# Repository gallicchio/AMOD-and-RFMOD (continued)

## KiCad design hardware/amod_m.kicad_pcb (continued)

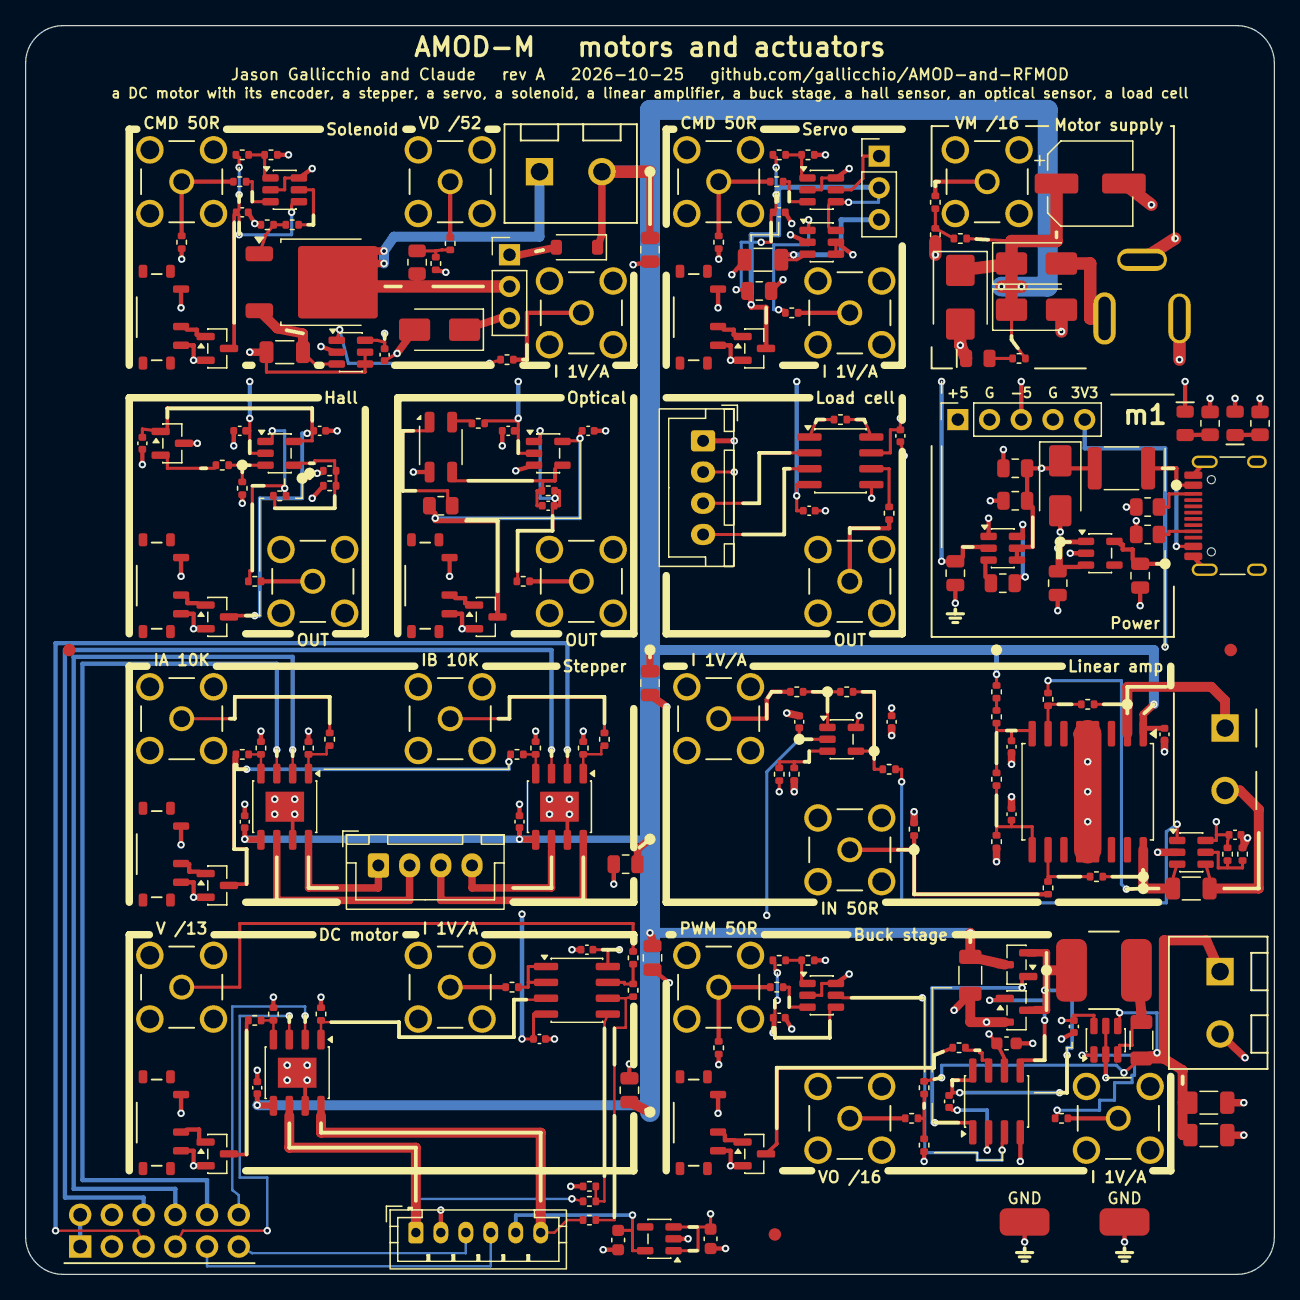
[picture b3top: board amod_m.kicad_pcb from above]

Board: 4 copper layers, 100.0 x 100.0 mm, 207 parts (0 on the bottom side), 126 nets.

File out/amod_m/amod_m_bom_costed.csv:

Comment,Designator,Footprint,LCSC Part #,MPN,Qty,Unit $,Ext $,JLC
220u,C201,CP_Elec_6.3x7.7,C2992606,XT220UF25V90RV0075,1,0.0534,0.053,extended
220n,C804,C_0402_1005Metric,C16772,CL05B224KO5NNNC,1,0.0047,0.005,basic
100p,C1001,C_0402_1005Metric,C1546,0402CG101J500NT,1,0.0033,0.003,basic
1u,"C105,C106",C_0805_2012Metric,C28323,CL21B105KBFNNNE,2,0.0341,0.068,basic
1u,"C305,C306,C805",C_0603_1608Metric,C15849,CL10A105KB8NNNC,3,0.0146,0.044,basic
22u,"C803,C806,C807",C_1206_3216Metric,C12891,CL31A226KAHNNNE,3,0.1673,0.502,basic
10u,"C101,C102,C103,C104,C302,C403,C502,C603,C701,C801",C_0805_2012Metric,C15850,CL21A106KAYNNNE,10,0.0426,0.426,basic
100n,"C301,C303,C304,C401,C402,C501,C601,C602,C702,C703,C704,C705,C706,C707,C802,C808,C901,C902,C903,C1002,C1003,C1101,C1102",C_0402_1005Metric,C1525,CL05B104KO5NNNC,23,0.0035,0.081,basic
SMAJ5.0A,D101,D_SMA,C78401,SMAJ5.0A,1,0.0537,0.054,extended
SMBJ16A,D201,D_SMB,C353386,SMBJ16A,1,0.0395,0.040,extended
B5819W,D601,D_SOD-123,C64885,B5819W,1,0.0195,0.019,extended
SMAJ24A,D602,D_SMA,C113962,SMAJ24A,1,0.0407,0.041,extended
SS34,"D202,D203",D_SMA,C8678,SS34,2,0.0351,0.070,basic
2A,F101,Fuse_1812_4532Metric,C210837,MF-MSMF200-2,1,0.0650,0.065,extended
USB-C,J101,USB_C_Receptacle_HRO_TYPE-C-31-M-12,C165948,TYPE-C-31-M-12,1,0.1888,0.189,extended
rails,J102,PinSocket_1x05_P2.54mm_Vertical,C2894928,PZ254-1-05-Z-8.5,1,0.0588,0.059,extended
5-16V,J202,BarrelJack_DC-005-5A_Horizontal,C381116,DC-005-5A-2.0,1,0.2631,0.263,extended
motor,J303,JST_PH_B6B-PH-K_1x06_P2.00mm_Vertical,C131342,B6B-PH-K-S(LF)(SN),1,0.0728,0.073,extended
Pmod,J304,PinHeader_2x06_P2.54mm_Horizontal_PZ254R-12-12P,C492434,PZ254R-12-12P,1,0.1036,0.104,extended
stepper,J403,JST_XH_B4B-XH-A_1x04_P2.50mm_Vertical,C144395,B4B-XH-A(LF)(SN),1,0.0569,0.057,extended
servo,J503,PinHeader_1x03_P2.54mm_Vertical,C2937625,PZ254V-11-03P,1,0.0199,0.020,extended
coil,J604,TerminalBlock_KF301_1x02_P5.00mm,C474881,KF301-5.0-2P,1,0.1017,0.102,extended
D Z,J605,PinHeader_1x03_P2.54mm_Vertical,C2937625,PZ254V-11-03P,1,0.0199,0.020,extended
load,J703,TerminalBlock_KF301_1x02_P5.00mm,C474881,KF301-5.0-2P,1,0.1017,0.102,extended
out,J804,TerminalBlock_KF301_1x02_P5.00mm,C474881,KF301-5.0-2P,1,0.1017,0.102,extended
cell,J1102,JST_XH_B4B-XH-A_1x04_P2.50mm_Vertical,C144395,B4B-XH-A(LF)(SN),1,0.0569,0.057,extended
SMA,"J201,J301,J302,J401,J402,J501,J502,J601,J602,J603,J701,J702,J801,J802,J803,J901,J1001,J1101",SMA_BWSMA-KE-Z001_Vertical,C496549,BWSMA-KE-Z001,18,0.4043,7.277,extended
47u,L801,L_6x6_SWPA6045,C36414,SWPA6045S470MT,1,0.0801,0.080,extended
-5V,LED101,LED_0805_2012Metric_Kbar,C84256,NCD0805R1,1,0.0135,0.013,basic
+5V,LED102,LED_0805_2012Metric_Kbar,C2297,KT-0805G,1,0.0164,0.016,basic
VM,LED201,LED_0805_2012Metric_Kbar,C2297,KT-0805G,1,0.0164,0.016,basic
NCE6020AK,Q602,TO-252-2,C108639,NCE6020AK,1,0.1560,0.156,extended
AO3400A,"Q802,Q803",SOT-23,C20917,AO3400A,2,0.0889,0.178,basic
AO3401A,"Q301,Q401,Q501,Q601,Q801,Q901,Q1001",SOT-23,C15127,AO3401A,7,0.0959,0.671,basic
4.7k,R204,R_0402_1005Metric,C25900,0402WGF4701TCE,1,0.0021,0.002,basic
1.5k,R302,R_0402_1005Metric,C25867,0402WGF1501TCE,1,0.0029,0.003,basic
0.1,R710,R_1206_3216Metric,C25334,1206W4F100LT5E,1,0.0080,0.008,basic
2k,R716,R_0402_1005Metric,C4109,0402WGF2001TCE,1,0.0026,0.003,basic
180,R1002,R_0805_2012Metric,C25270,0805W8F1800T5E,1,0.0031,0.003,extended
249,R1101,R_0402_1005Metric,C25096,0402WGF2490TCE,1,0.0015,0.002,extended
1k,"R103,R104",R_0805_2012Metric,C17513,0805W8F1001T5E,2,0.0035,0.007,basic
13k,"R308,R309",R_0402_1005Metric,C25754,0402WGF1302TCE,2,0.0023,0.005,extended
100k,"R606,R805",R_0402_1005Metric,C25741,0402WGF1003TCE,2,0.0015,0.003,basic
100,"R610,R1001",R_0402_1005Metric,C25076,0402WGF1000TCE,2,0.0012,0.002,basic
5.1k,"R101,R102,R609",R_0805_2012Metric,C27834,0805W8F5101T5E,3,0.0036,0.011,basic
620,"R303,R403,R406",R_0402_1005Metric,C4961,0402WGF6200TCE,3,0.0019,0.006,extended
47k,"R503,R603,R803",R_0402_1005Metric,C25792,0402WGF4702TCE,3,0.0020,0.006,basic
5.1k,"R504,R604,R804",R_0402_1005Metric,C25905,0402WGF5101TCE,3,0.0023,0.007,basic
0.05,"R505,R607,R806",R_1206_3216Metric,C127691,1206W3F500MT5E,3,0.0110,0.033,extended
15k,"R203,R701,R702,R808",R_0402_1005Metric,C25756,0402WGF1502TCE,4,0.0010,0.004,basic
3.9k,"R402,R405,R902,R905",R_0402_1005Metric,C51721,0402WGF3901TCE,4,0.0012,0.005,extended
20k,"R703,R707,R713,R903,R904",R_0402_1005Metric,C25765,0402WGF2002TCE,5,0.0011,0.006,basic
1k,"R202,R301,R305,R307,R401,R404,R711,R712,R809,R1003",R_0402_1005Metric,C11702,0402WGF1001TCE,10,0.0013,0.013,basic
10k,"R407,R408,R502,R602,R704,R706,R708,R709,R714,R715,R802,R901",R_0402_1005Metric,C25744,0402WGF1002TCE,12,0.0011,0.013,basic
49.9,"R201,R304,R306,R501,R506,R601,R605,R608,R611,R705,R717,R801,R807,R810,R906,R1004,R1102",R_0402_1005Metric,C844112,CRCW040249R9FKEDHP,17,0.0318,0.541,extended
ON,"SW301,SW401,SW501,SW601,SW801,SW901,SW1001",SW_SPDT_Shouhan_MSK12C02,C431540,MSK12C02,7,0.0529,0.370,extended
GND,"TP9901,TP9902",TestPoint_Loop_RH-5019,C5199800,RH-5019,2,0.0966,0.193,extended
LM2664,U101,SOT-23-6,C108573,LM2664M6X/NOPB,1,0.3346,0.335,extended
OPA2171,U302,SOIC-8_3.9x4.9mm_P1.27mm,C40904,OPA2171AIDR,1,0.3423,0.342,extended
TCA0372,U701,SOIC-16W_7.5x10.3mm_P1.27mm,C362060,TCA0372DWR2G,1,1.1775,1.177,extended
TPS28225,U802,SOIC-8_3.9x4.9mm_P1.27mm,C52897,TPS28225DR,1,0.8565,0.857,extended
DRV5055,U901,SOT-23,C266128,DRV5055A3QDBZR,1,0.5241,0.524,extended
QRE1113,U1001,OnSemi_CASE100CY,C232862,QRE1113GR,1,0.7354,0.735,extended
INA828,U1101,SOIC-8_3.9x4.9mm_P1.27mm,C544342,INA828IDR,1,1.5394,1.539,extended
3.3V,"U102,U303",SOT-23-5,C2862740,TPS7A2033PDBVR,2,0.2097,0.419,extended
DRV8251A,"U301,U401,U402",HSOP-8-1EP_3.9x4.9mm_P1.27mm_EP2.41x3.1mm,C5218844,DRV8251ADDAR,3,0.4420,1.326,extended
TLV3501,"U501,U601,U801",SOT-23-6,C193413,TLV3501AIDBVR,3,1.9246,5.774,extended
OPA810,"U703,U902,U1002",SOT-23-5,C2833513,OPA810IDBVR,3,3.0996,9.299,extended
INA181,"U502,U602,U702,U803",SOT-23-6,C2058943,INA181A1IDBVR,4,0.4717,1.887,extended
